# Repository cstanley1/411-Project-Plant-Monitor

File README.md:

# 411 Project: Happy Plant

Happy Plant is designed to help keep track of a plant’s health. Simply plant your plant in the Happy Plant Planter, and the light-up display will tell you when it's time to water!

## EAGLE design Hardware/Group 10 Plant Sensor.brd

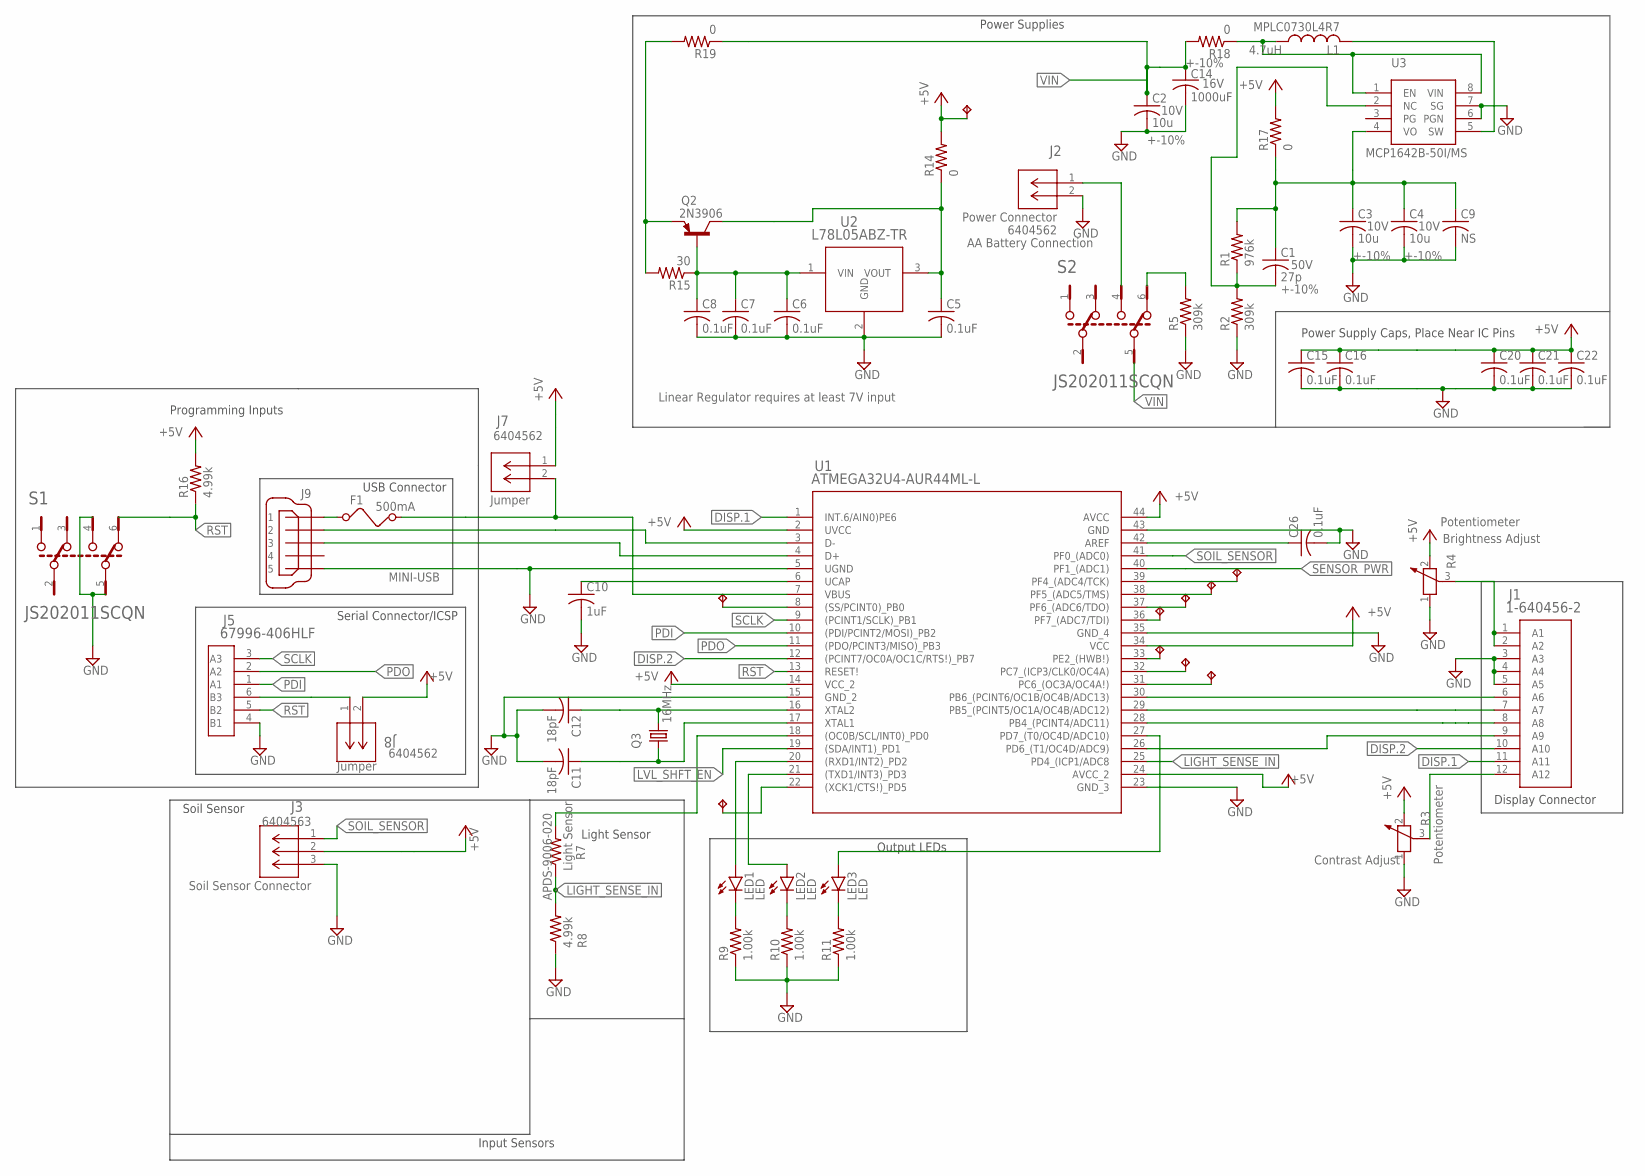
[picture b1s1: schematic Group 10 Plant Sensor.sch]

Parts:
C1: 27p; C0805K; VOLTAGE 50V; MFG_PART_NUMBER C0805C270J1GACTU
C2, C3, C4: 10u; C0805K; VOLTAGE 10V; MFG_PART_NUMBER GRM21BR61D106ME15L
C5, C6, C7, C8, C15, C16, C20, C21, C22, C26: 0.1uF; C0805; MFG_PART_NUMBER C0805C104K6RACTU
C9: NS; C0603K
C10: 1uF; C0805K; MFG_PART_NUMBER LMK212BJ105KD-T
C11, C12: 18pF; C0805K; MFG_PART_NUMBER GRM21A5C2E180JW01D
C14: 1000uF; C050-050X075; VOLTAGE 16V; MFG_PART_NUMBER EEU-FS1A102B
F1: 500mA; R1206; MFG_PART_NUMBER CC12H500MA-TR
J1: 1-640456-2; MFG_PART_NUMBER 1-640456-2
J2, J7, J8: 640456-2; CONN2_640456-2; MFG_PART_NUMBER 640456-2
J3: 640456-3; CONN3_640456-3; MFG_PART_NUMBER 640456-3
J5: 67996-406HLF; MFG_PART_NUMBER 67996-406HLF
J9: MINI-USB; 32005-201; MFG_PART_NUMBER UJ2-MABH-2-SMT-TR
L1: MPLC0730L4R7; MFG_PART_NUMBER NPIM74C4R7MTRF
LED1, LED2, LED3: LED; LED3MM; MFG_PART_NUMBER WP7113SRD/J4
Q2: 2N3906; TO92; MFG_PART_NUMBER 2N3906
Q3: 16MHz; HC18U-V; MFG_PART_NUMBER FC4STCBAF16.0-BAG200
R1: 976k; R0805; MFG_PART_NUMBER ERA-6AEB9763V
R2, R5: 309k; R0805; MFG_PART_NUMBER ERA-6AEB3093V
R3, R4: Potentiometer; PT-10S; MFG_PART_NUMBER PT10LH01-102A2020
R7: Light Sensor; R1206W; MFG_PART_NUMBER APDS-9006-020
R8, R16: 4.99k; R1206W; MFG_PART_NUMBER ERJ-PB6B4991V
R9, R10, R11: 1.00k; R0805; MFG_PART_NUMBER CRGH0805J1K0
R14, R17, R18, R19: 0; R0603; MFG_PART_NUMBER CRCW08050000Z0EBC
R15: 30; R0805; MFG_PART_NUMBER ERA-6AEB3093V
S1, S2: SWITCH2; C&K_JS202011CQN_0; MFG_PART_NUMBER JS202011SCQN
U1: ATMEGA32U4-AUR44ML-L; 44ML-L; MFG_PART_NUMBER ATMEGA32U4-AUR
U2: L78L05ABZ-TR; TO-92-TR; MFG_PART_NUMBER L78L05ABZ
U3: MCP1642B/D8-MSOP; MSOP8; MFG_PART_NUMBER MCP1642B-50I/MS
U$3, U$4, U$5, U$6, U$7, U$8, U$9, U$10, U$11, U$12: TESTPIN; 1-640456-0(2)

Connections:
AREF: C26.1, U1.42 (AREF)
DISP.1: J1.11 (A11), U1.1 (INT.6/AIN0)PE6)
DISP.2: J1.10 (A10), U1.12 ((PCINT7/OC0A/OC1C/RTS!)_PB7)
DISP_5: J1.8 (A8), U1.28 (PB4_(PCINT4/ADC11))
GND: C2.2, C3.2, C4.2, C5.2, C6.2, C7.2, C8.2, C9.2, C10.2, C11.2, C12.2, C14.2, C15.2, C16.2, C20.2, C21.2, C22.2, C26.2, J1.3 (A3), J1.4 (A4), J1.5 (A5), J2.2, J3.3, J5.4 (B1), J9.5, R2.1, R3.1, R4.1, R5.1, R8.1, R9.1, R10.1, R11.1, S1.4, S1.5, U1.5 (UGND), U1.15 (GND_2), U1.23 (GND_3), U1.35 (GND_4), U1.43 (GND), U2.2 (GND), U3.6 (PGN), U3.7 (SG)
LIGHT_SENSE_IN: R7.1, R8.2, U1.25 (PD4_(ICP1/ADC8)
LIGHT_SENSE_PWR: R7.2, U1.18 ((OC0B/SCL/INT0)_PD0)
LVL_SHFT_EN: U1.19 ((SDA/INT1)_PD1)
unnamed: J1.12 (A12), R3.3
unnamed: L1.2, U3.5 (SW)
unnamed: J1.9 (A9), U1.26 (PD6_(T1/OC4D/ADC9))
unnamed: C12.1, Q3.2, U1.16 (XTAL2)
unnamed: J1.6 (A6), U1.30 (PB6_(PCINT6/OC1B/OC4B/ADC13))
unnamed: J1.7 (A7), U1.29 (PB5_(PCINT5/OC1A/OC4B/ADC12))
unnamed: C11.1, Q3.1, U1.17 (XTAL1)
unnamed: J9.2, U1.3 (D-)
unnamed: J9.3, U1.4 (D+)
unnamed: F1.1, J9.1
unnamed: LED3.K (C), R11.2
unnamed: C1.1, C3.1, C4.1, C9.1, R1.2, R17.1, U3.4 (VO)
unnamed: J1.1 (A1), J1.2 (A2), R4.3
unnamed: C6.1, C7.1, C8.1, Q2.2 (B), R15.1, U2.1 (VIN)
unnamed: C10.1, U1.6 (UCAP)
unnamed: C5.1, Q2.1 (C), R14.1, U2.3 (VOUT)
unnamed: LED2.K (C), R10.2
unnamed: J5.6 (B3), J8.1
unnamed: LED1.K (C), R9.2
unnamed: U1.8 ((SS/PCINT0)_PB0), U$12.1
unnamed: R5.2, S2.6
unnamed: LED1.A, U1.20 ((RXD1/INT2)_PD2)
unnamed: LED2.A, U1.21 ((TXD1/INT3)_PD3)
unnamed: LED3.A, U1.27 (PD7_(T0/OC4D/ADC10))
unnamed: U1.31 (PC6_(OC3A/OC4A!)), U$10.1
unnamed: Q2.3 (E), R15.2, R19.2
unnamed: U1.32 (PC7_(ICP3/CLK0/OC4A)), U$9.1
unnamed: J2.1, S2.4
unnamed: U1.33 (PE2_(HWB!)), U$8.1
unnamed: U1.36 (PF7_(ADC7/TDI)), U$7.1
unnamed: U1.37 (PF6_(ADC6/TDO)), U$6.1
unnamed: U1.22 ((XCK1/CTS!)_PD5), U$11.1
unnamed: U1.38 (PF5_(ADC5/TMS)), U$5.1
unnamed: U1.39 (PF4_(ADC4/TCK)), U$4.1
PDI: J5.1 (A1), U1.10 ((PDI/PCINT2/MOSI)_PB2)
PDO: J5.2 (A2), U1.11 ((PDO/PCINT3/MISO)_PB3)
RST: J5.5 (B2), R16.1, S1.6, U1.13 (RESET!)
SCLK: J5.3 (A3), U1.9 ((PCINT1/SCLK)_PB1)
SENSOR_PWR: U1.40 (PF1_(ADC1))
SOIL_SENSOR: J3.1, U1.41 (PF0_(ADC0))
SWITCH: L1.1, R18.1, U3.1 (EN), U3.8 (VIN)
VBUS: F1.2, J7.2, U1.7 (VBUS)
VCC: C15.1, C16.1, C20.1, C21.1, C22.1, J3.2, J7.1, J8.2, R3.2, R4.2, R14.2, R16.2, R17.2, U1.2 (UVCC), U1.14 (VCC_2), U1.24 (AVCC_2), U1.34 (VCC), U1.44 (AVCC), U$3.1
VFB: C1.2, R1.1, R2.2, U3.2 (NC)
VIN: C2.1, C14.1, R18.2, R19.1, S2.5

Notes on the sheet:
Power Supplies
USB Connector
Serial Connector/ICSP
Soil Sensor
Light Sensor
Programming Inputs
Input Sensors
Output LEDs
Display Connector
Power Supply Caps, Place Near IC Pins
AA Battery Connection
Contrast Adjust
Brightness Adjust
Linear Regulator requires at least 7V input

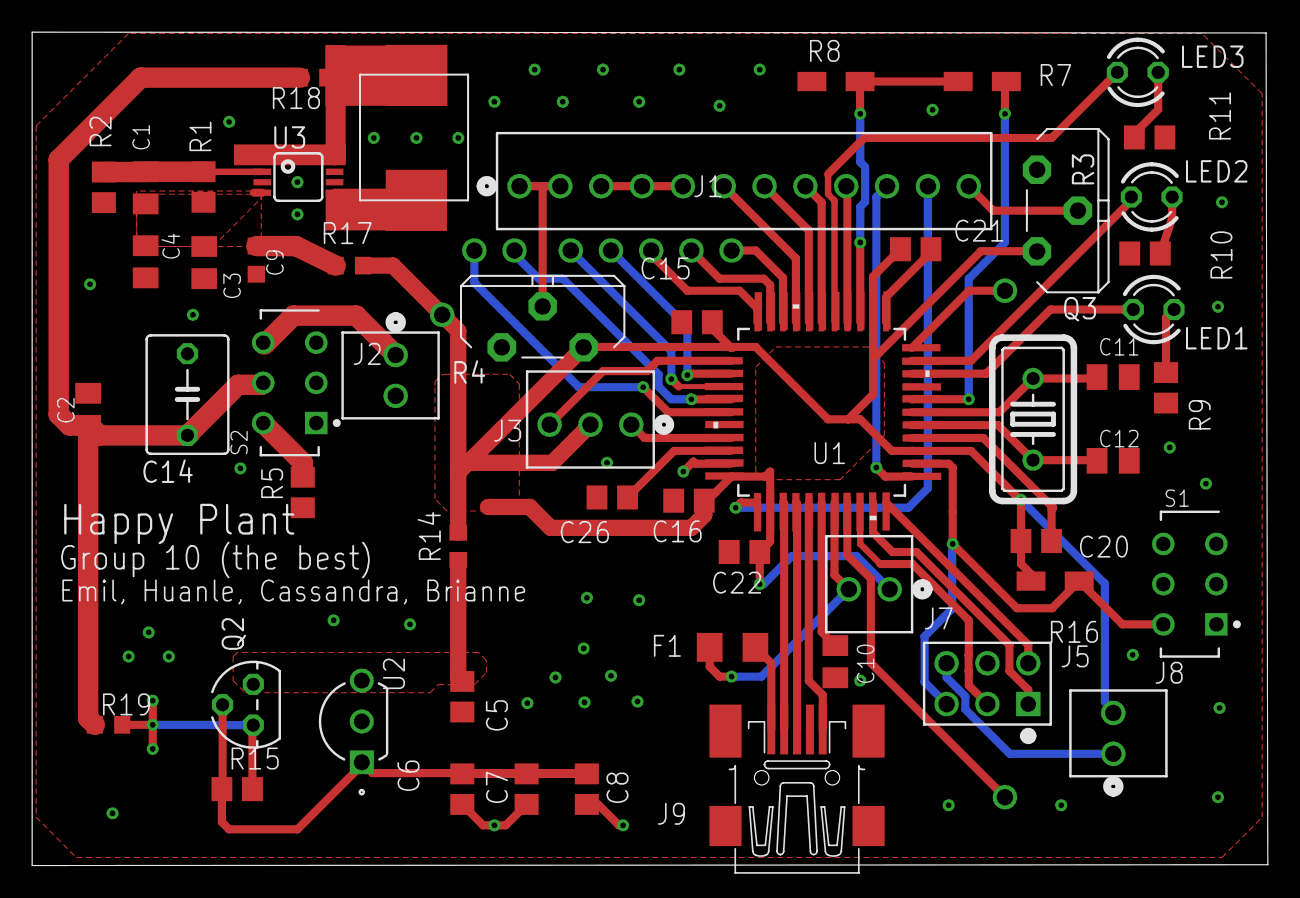
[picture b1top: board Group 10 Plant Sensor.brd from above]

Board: 2 copper layers, 76.8 x 51.8 mm, 64 parts (0 on the bottom side), 51 nets.

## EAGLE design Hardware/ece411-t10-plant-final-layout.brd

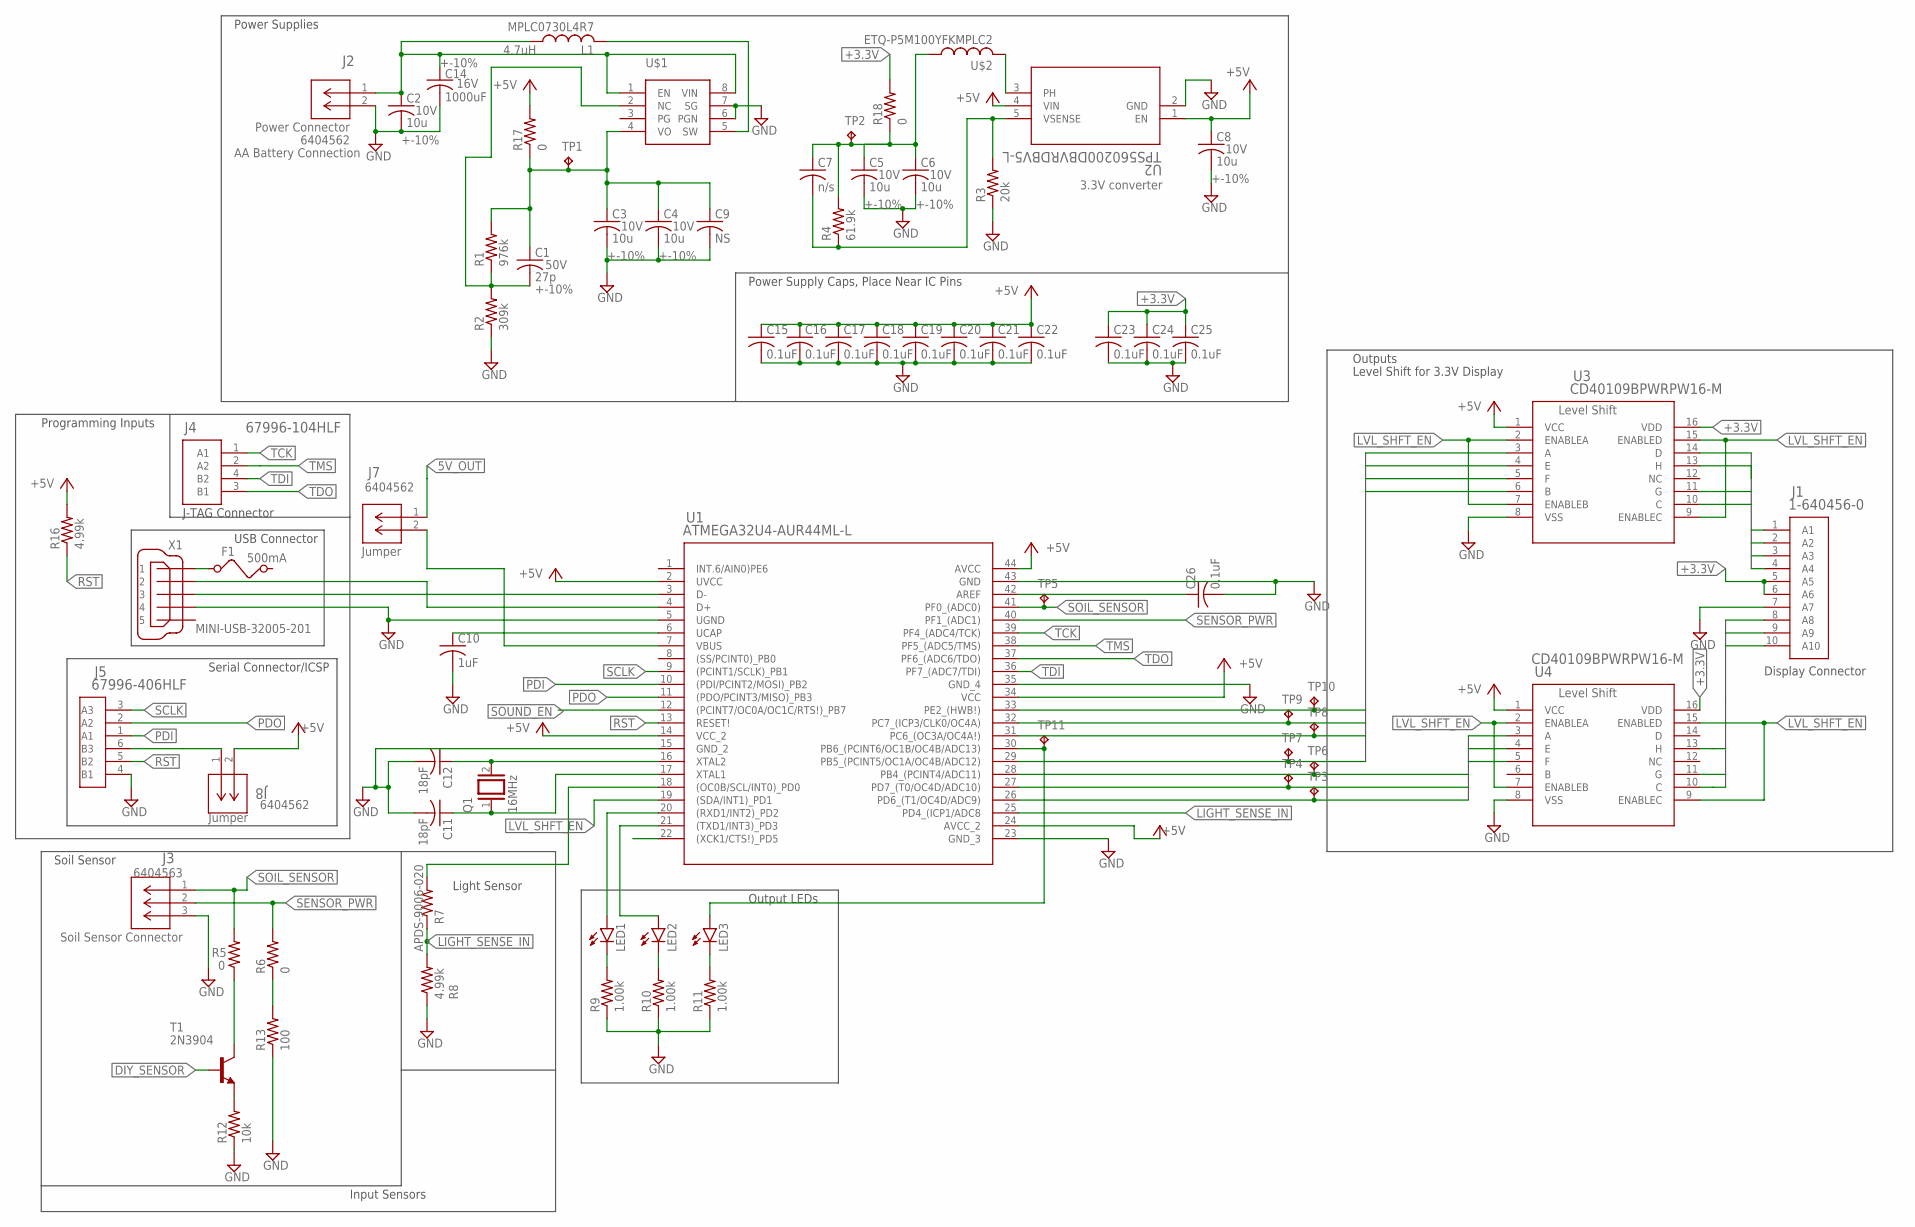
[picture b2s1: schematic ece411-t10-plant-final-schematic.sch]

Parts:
C1: 27p; C0805K; VOLTAGE 50V; MFG_PART_NUMBER C0805C270J1GACTU
C2, C3, C4, C5, C6, C8: 10u; C0805K; VOLTAGE 10V; MFG_PART_NUMBER GRM21BR61D106ME15L
C7: n/s; C0805K
C9: NS; C0603K
C10: 1uF; C0805K; MFG_PART_NUMBER LMK212BJ105KD-T
C11, C12: 18pF; C0805K; MFG_PART_NUMBER GRM21A5C2E180JW01D
C14: 1000uF; C050-050X075; VOLTAGE 16V; MFG_PART_NUMBER EEU-FS1A102B
C15, C16, C17, C18, C19, C20, C21, C22, C23, C24, C25, C26: 0.1uF; C0805; MFG_PART_NUMBER C0805C104K6RACTU
F1: 500mA; R1206; MFG_PART_NUMBER CC12H500MA-TR
J1: 1-640456-0; MFG_PART_NUMBER 1-640456-0
J2, J7, J8: 640456-2; CONN2_640456-2; MFG_PART_NUMBER 640456-2
J3: 640456-3; CONN3_640456-3; MFG_PART_NUMBER 640456-3
J4: 67996-104HLF; MFG_PART_NUMBER 67996-404HLF
J5: 67996-406HLF; MFG_PART_NUMBER 67996-406HLF
L1: MPLC0730L4R7; MFG_PART_NUMBER NPIM74C4R7MTRF
LED1, LED2, LED3: LED3MM; MFG_PART_NUMBER WP7113SRD/J4
Q1: 16MHz; Q; MFG_PART_NUMBER FC4STCBAF16.0-BAG200
R1: 976k; R0805; MFG_PART_NUMBER ERA-6AEB9763V
R2: 309k; R0805; MFG_PART_NUMBER ERA-6AEB3093V
R3: 20k; R0805; MFG_PART_NUMBER ERA6AEB203V
R4: 61.9k; R0805; MFG_PART_NUMBER RC2012F6192CS
R5, R6, R17, R18: 0; R0603; MFG_PART_NUMBER CRCW08050000Z0EBC
R7: R-US_R1206W; R1206W; MFG_PART_NUMBER APDS-9006-020
R8, R16: 4.99k; R1206W; MFG_PART_NUMBER ERJ-PB6B4991V
R9, R10, R11: 1.00k; R0805; MFG_PART_NUMBER CRGH0805J1K0
R12: 10k; M1206; MFG_PART_NUMBER CRGH0805J10K
R13: 100; M1206; MFG_PART_NUMBER CRCW0805100RFKEAC
T1: 2N3904; TO92; MFG_PART_NUMBER 2N3904TF
TP1, TP2, TP3, TP4, TP5, TP6, TP7, TP8, TP9, TP10, TP11: TPPAD1-20; P1-20
U1: ATMEGA32U4-AUR44ML-L; 44ML-L
U2: TPS560200DBVRDBV5-L; DBV5-L
U3, U4: CD40109BPWRPW16-M; PW16-M; MFG_PART_NUMBER CD40109BPW
U$1: MCP1642B/D8-MSOP; MSOP8; MFG_PART_NUMBER MCP1642B-50I/MS
U$2: ETQ-P5M100YFKMPLC2; PA4346.103ANLT
X1: MINI-USB-32005-201; 32005-201; MFG_PART_NUMBER UJ2-MABH-2-SMT-TR

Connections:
5V_OUT: J7.1
+3.3V: C7.1, C23.1, C24.1, C25.1, J1.5 (A5), J1.6 (A6), R4.2, TP2.TP, U3.16 (VDD), U4.16 (VDD)
AREF: C26.1, U1.42 (AREF)
DISP_1: TP10.TP, U1.33 (PE2_(HWB!)), U3.3 (A)
DISP_2: TP9.TP, U1.32 (PC7_(ICP3/CLK0/OC4A)), U3.4 (E)
DISP_3: TP8.TP, U1.31 (PC6_(OC3A/OC4A!)), U3.5 (F)
DISP_5: TP6.TP, U1.28 (PB4_(PCINT4/ADC11)), U4.3 (A)
DISP_6: TP4.TP, U1.27 (PD7_(T0/OC4D/ADC10)), U4.4 (E)
DISP_7: TP3.TP, U1.26 (PD6_(T1/OC4D/ADC9)), U4.5 (F)
DIY_SENSOR: T1.2 (B)
GND: C2.2, C3.2, C4.2, C5.2, C6.2, C8.2, C9.2, C10.2, C11.2, C12.2, C14.2, C15.2, C16.2, C17.2, C18.2, C19.2, C20.2, C21.2, C22.2, C23.2, C24.2, C25.2, C26.2, J1.7 (A7), J2.2, J3.3, J5.4 (B1), R2.1, R3.1, R8.1, R9.1, R10.1, R11.1, R12.1, R13.1, U1.15 (GND_2), U1.23 (GND_3), U1.35 (GND_4), U1.43 (GND), U2.2 (GND), U3.8 (VSS), U4.8 (VSS), U$1.6 (PGN), U$1.7 (SG)
LIGHT_SENSE_IN: R7.1, R8.2, U1.25 (PD4_(ICP1/ADC8)
LIGHT_SENSE_PWR: R7.2, U1.18 ((OC0B/SCL/INT0)_PD0)
LVL_SHFT_EN: U1.19 ((SDA/INT1)_PD1), U3.2 (ENABLEA), U3.7 (ENABLEB), U3.9 (ENABLEC), U3.15 (ENABLED), U4.2 (ENABLEA), U4.7 (ENABLEB), U4.9 (ENABLEC), U4.15 (ENABLED)
unnamed: U2.3 (PH), U$2.P$2 (2)
unnamed: L1.2, U$1.5 (SW)
unnamed: C7.2, R3.2, R4.1, U2.5 (VSENSE)
unnamed: U1.5 (UGND), X1.4
unnamed: C12.1, Q1.2, U1.16 (XTAL2)
unnamed: TP7.TP, U1.29 (PB5_(PCINT5/OC1A/OC4B/ADC12)), U3.6 (B)
unnamed: C11.1, Q1.1, U1.17 (XTAL1)
unnamed: U1.4 (D+), X1.2
unnamed: U1.3 (D-), X1.3
unnamed: F1.1, X1.1
unnamed: LED3.K (C), R11.2
unnamed: C1.1, C3.1, C4.1, C9.1, R1.2, R17.1, TP1.TP, U$1.4 (VO)
unnamed: J1.8 (A8), U4.10 (C)
unnamed: J1.9 (A9), U4.11 (G)
unnamed: C10.1, U1.6 (UCAP)
unnamed: J1.1 (A1), U3.14 (D)
unnamed: LED2.K (C), R10.2
unnamed: J5.6 (B3), J8.1
unnamed: LED1.K (C), R9.2
unnamed: R5.1, T1.1 (C)
unnamed: R12.2, T1.3 (E)
unnamed: LED1.A, U1.20 ((RXD1/INT2)_PD2)
unnamed: LED2.A, U1.21 ((TXD1/INT3)_PD3)
unnamed: LED3.A, TP11.TP, U1.30 (PB6_(PCINT6/OC1B/OC4B/ADC13))
unnamed: R6.1, R13.2
unnamed: J1.2 (A2), U3.13 (H)
unnamed: J1.3 (A3), U3.11 (G)
unnamed: J1.4 (A4), U3.10 (C)
unnamed: J1.10 (A10), U4.13 (H)
unnamed: C5.1, C6.1, R18.1, U$2.P$1 (1)
PDI: J5.1 (A1), U1.10 ((PDI/PCINT2/MOSI)_PB2)
PDO: J5.2 (A2), U1.11 ((PDO/PCINT3/MISO)_PB3)
RST: J5.5 (B2), R16.1, U1.13 (RESET!)
SCLK: J5.3 (A3), U1.9 ((PCINT1/SCLK)_PB1)
SENSOR_PWR: J3.2, R6.2, U1.40 (PF1_(ADC1))
SOIL_SENSOR: J3.1, R5.2, TP5.TP, U1.41 (PF0_(ADC0))
SOUND_EN: U1.12 ((PCINT7/OC0A/OC1C/RTS!)_PB7)
SWITCH: C2.1, C14.1, J2.1, L1.1, U$1.1 (EN), U$1.8 (VIN)
TCK: J4.1 (A1), U1.39 (PF4_(ADC4/TCK))
TDI: J4.4 (B2), U1.36 (PF7_(ADC7/TDI))
TDO: J4.3 (B1), U1.37 (PF6_(ADC6/TDO))
TMS: J4.2 (A2), U1.38 (PF5_(ADC5/TMS))
VBUS: J7.2, U1.7 (VBUS)
VCC: C8.1, C15.1, C16.1, C17.1, C18.1, C19.1, C20.1, C21.1, C22.1, J8.2, R16.2, R17.2, U1.2 (UVCC), U1.14 (VCC_2), U1.24 (AVCC_2), U1.34 (VCC), U1.44 (AVCC), U2.1 (EN), U2.4 (VIN), U3.1 (VCC), U4.1 (VCC)
VFB: C1.2, R1.1, R2.2, U$1.2 (NC)

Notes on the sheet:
Power Supplies
USB Connector
Serial Connector/ICSP
Soil Sensor
Light Sensor
J-TAG Connector
Programming Inputs
Input Sensors
Output LEDs
Level Shift for 3.3V Display
Display Connector
Power Supply Caps, Place Near IC Pins
Outputs
AA Battery Connection

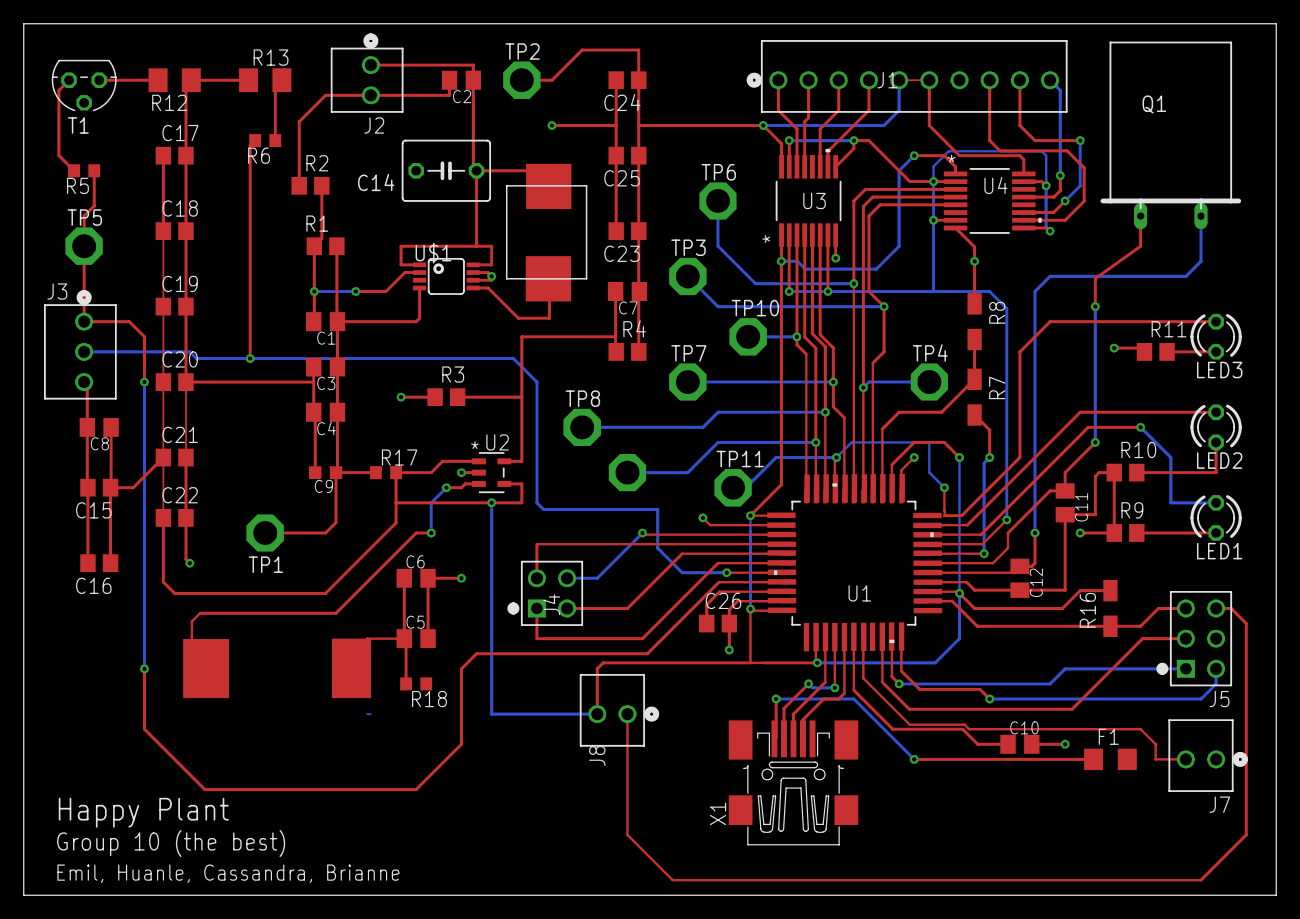
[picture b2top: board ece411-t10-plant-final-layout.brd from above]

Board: 2 copper layers, 105.4 x 73.3 mm, 73 parts (1 on the bottom side), 56 nets.

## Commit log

2018-10-14 Schematic Rough Draft
    the board has circuits to support: a soil moisture sensor, a DIY soil sensor, 3 LEDs, an ambient light sensor, a display, USB connectivity, and audio output (rough). The board allows programming with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
2018-10-24 Updated Schematic
2018-11-01 Components list
2018-11-08 Team 6 Review
    We got together with team 6 and documented the review updated here.
2018-11-08 Create Board Layout
2018-12-03 Rename Group 10 Plant Sensor.brd to Hardware/Group 10 Plant Sensor.brd
2018-12-03 Rename ece411-t10-plant-final-layout.brd to Hardware/ece411-t10-plant-final-layout.brd
2018-12-03 Rename ece411-t10-plant-final-schematic.sch to Hardware/ece411-t10-plant-final-schematic.sch
2018-12-03 moved to hardware folder
2018-12-03 Moved to /Hardware/Datasheets
2018-12-03 Moving to Hardware
2018-12-03 Moving to Harware File
2018-12-03 Moved to /Project Files
2018-12-03 Updated as Group 10 Plant Sensor BOM
2018-12-03 Updated to new new layout
2018-12-03 updated to new new schematic
2018-12-06 Create LICENSE
